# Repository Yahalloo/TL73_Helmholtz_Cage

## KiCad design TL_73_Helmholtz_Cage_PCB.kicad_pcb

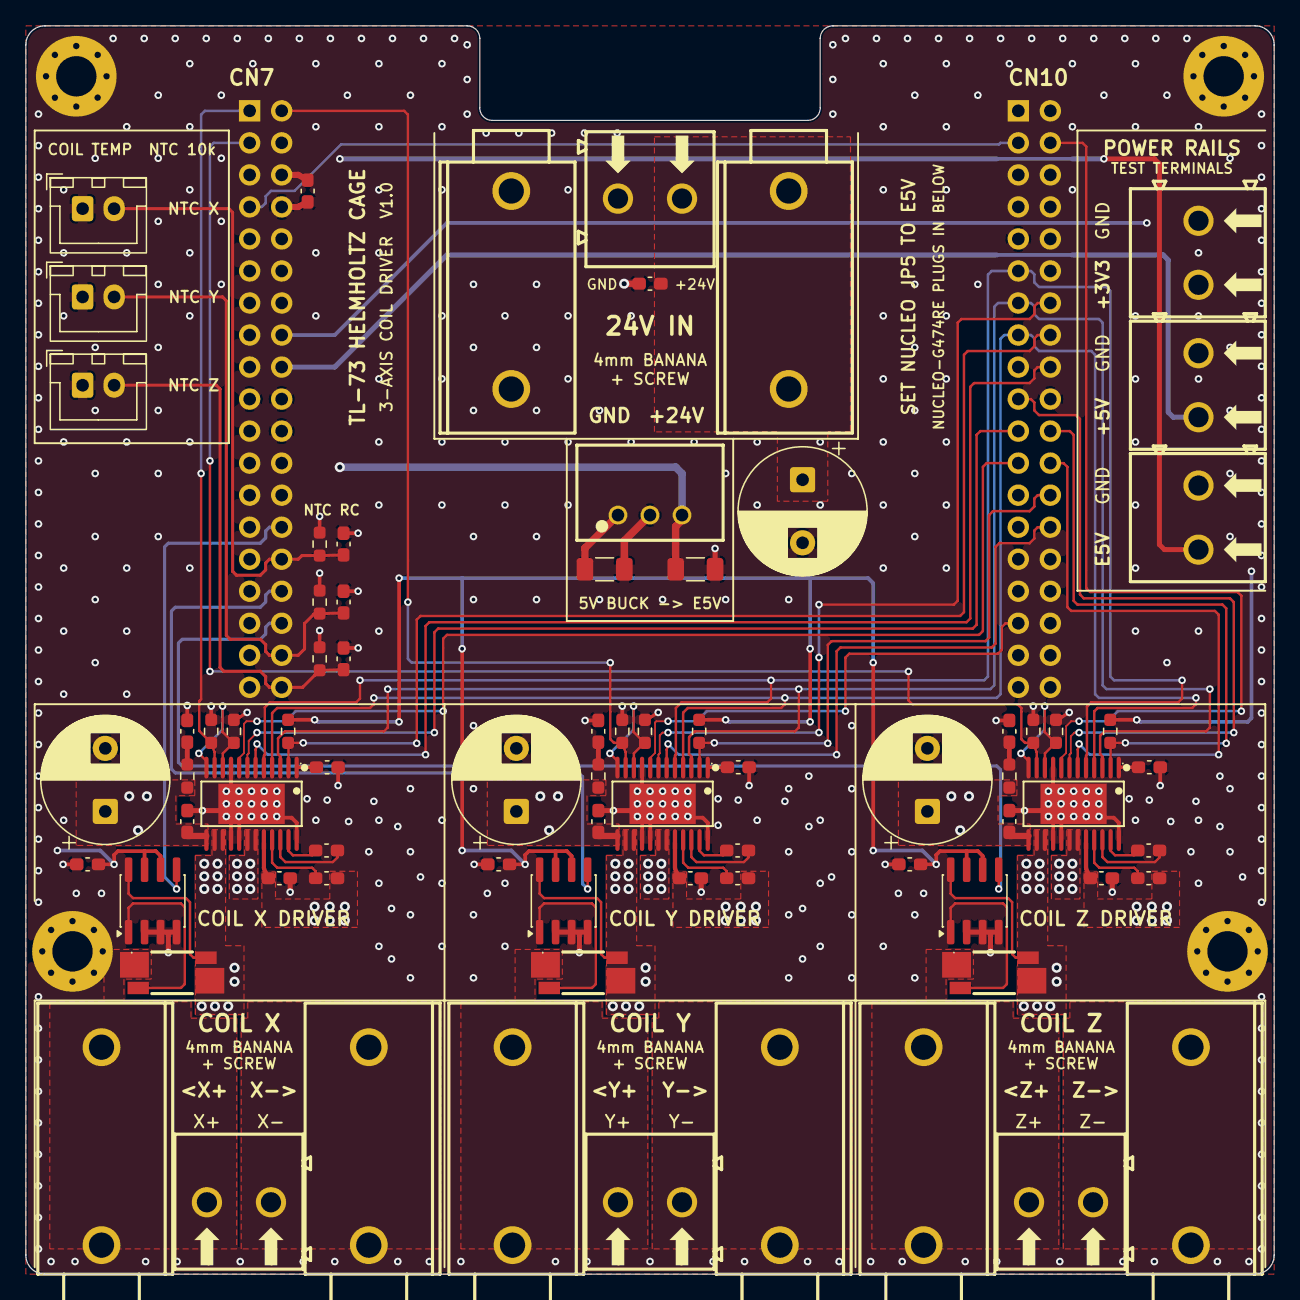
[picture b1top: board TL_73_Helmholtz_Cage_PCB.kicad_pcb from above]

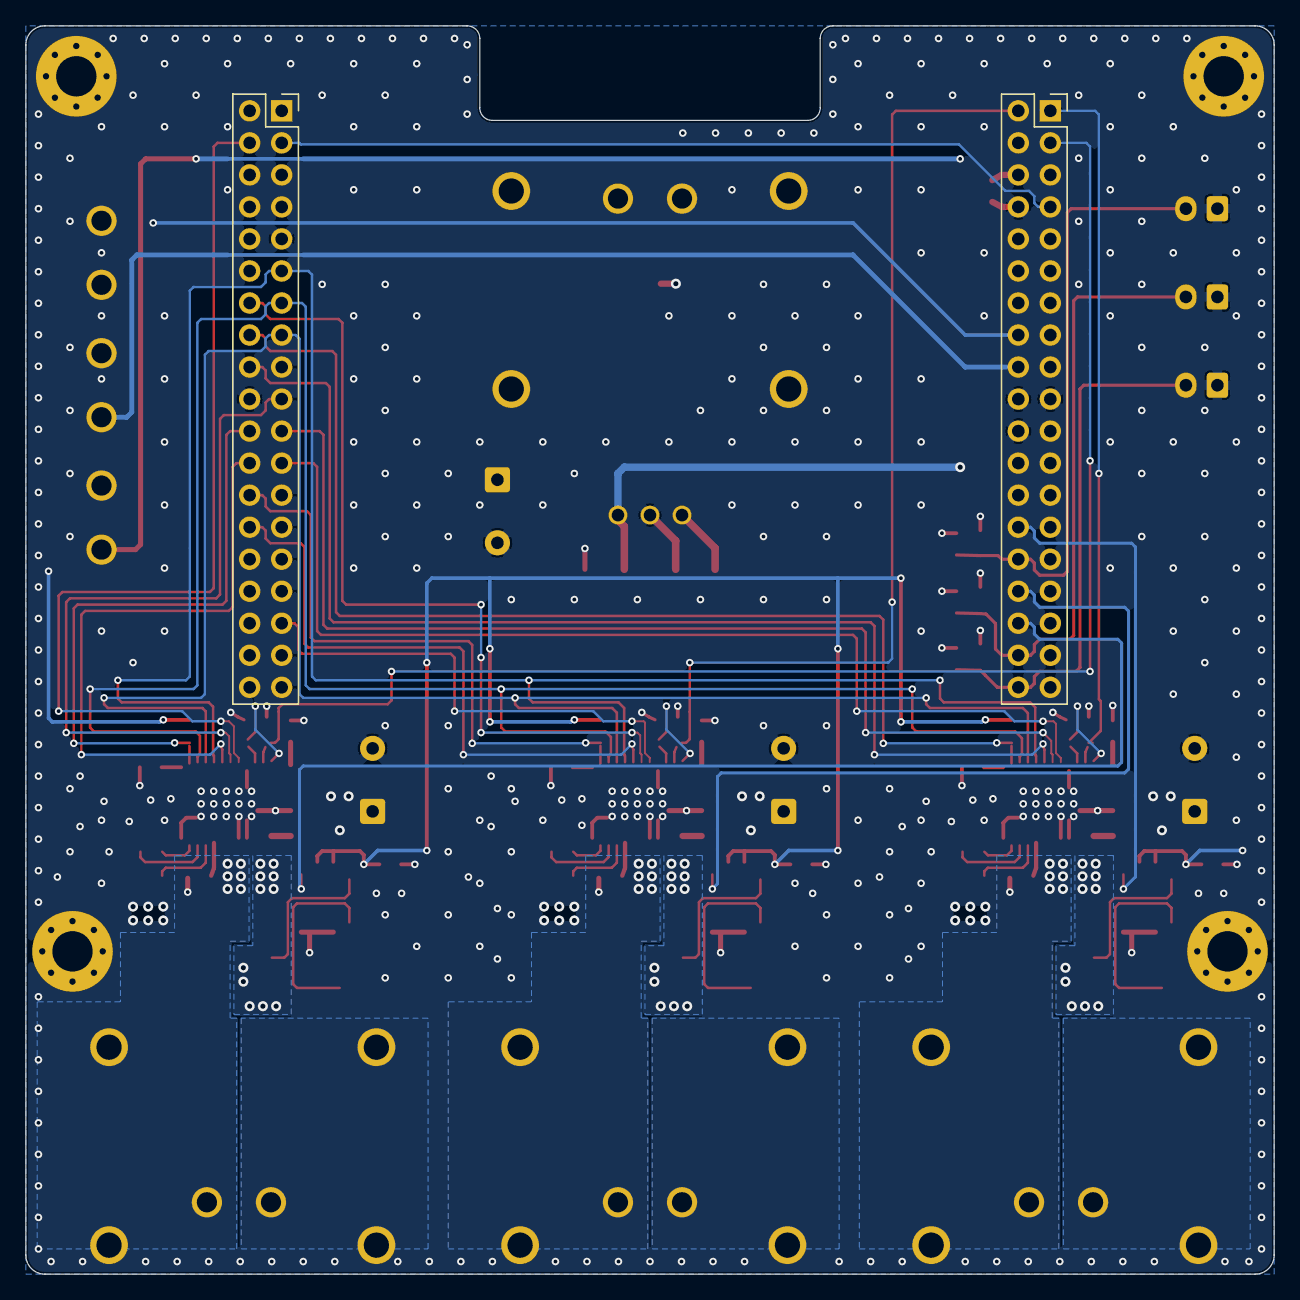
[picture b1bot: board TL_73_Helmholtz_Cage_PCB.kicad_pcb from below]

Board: 4 copper layers, 99.0 x 99.0 mm, 81 parts (2 on the bottom side), 63 nets.

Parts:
C101: 10uF; C_1206_3216Metric_Pad1.33x1.80mm_HandSolder
C102: 22uF; C_1206_3216Metric_Pad1.33x1.80mm_HandSolder
C201, C302, C305, C402, C405, C502, C505, C601, C701, C801, C901, C1001, C1101, C1202: 100nF; C_0603_1608Metric_Pad1.08x0.95mm_HandSolder
C301, C304, C401, C404, C501, C504: 1uF; C_0603_1608Metric_Pad1.08x0.95mm_HandSolder
C303, C403, C503: 47nF; C_0603_1608Metric_Pad1.08x0.95mm_HandSolder
C306, C406, C506: 10nF; C_0603_1608Metric_Pad1.08x0.95mm_HandSolder
C307, C407, C507, C1201: 1000uF; CP_Radial_D10.0mm_P5.00mm
CN1201: 24.243.1; CONN-TH_24.243.1_RED
CN1202: 24.243.2; CONN-TH_24.243.2
CN1203, CN1205, CN1207: 24.243.3; CONN-TH_24.243.3
CN1204, CN1206, CN1208: 24.243.5; CONN-TH_24.243.2
H101, H102, H103, H104: MountingHole; MountingHole_3.2mm_M3_Pad_Via
J201: CN7; PinSocket_2x19_P2.54mm_Vertical
J202: CN10; PinSocket_2x19_P2.54mm_Vertical
J901, J1001, J1101: NTC_JST_XH; JST_XH_B2B-XH-A_1x02_P2.50mm_Vertical
R301, R302, R401, R402, R501, R502, R901, R1001, R1101: 10k; R_0603_1608Metric_Pad0.98x0.95mm_HandSolder
R303, R403, R503: 470Ω; R_0603_1608Metric_Pad0.98x0.95mm_HandSolder
R304, R404, R504: 3.3Ω; R_0603_1608Metric_Pad0.98x0.95mm_HandSolder
R601, R701, R801: 10mΩ; RES-SMD_L6.4-W3.2_WSK2512R0100FEA
U101: K7805-1000R3_C2992391; PWRM-TH_YLPTEC_K78XX-1000R3
U301, U401, U501: DRV8873SPWPR; HTSSOP-24_L7.8-W4.4-P0.65-LS6.4-TL-EP
U601, U701, U801: INA240A1D; SOIC-8_3.9x4.9mm_P1.27mm
U1201, U1202, U1203, U1204, U1205, U1206, U1207: KF128-5.08-2P; CONN-TH_P5.08_KF128-5.08-2P

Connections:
+3V3: C601.1, C701.1, C801.1, J201.16, R301.1, R401.1, R501.1, R901.2, R1001.2, R1101.2, U601.6 (V+), U601.7 (REF1), U701.6 (V+), U701.7 (REF1), U801.6 (V+), U801.7 (REF1), U1207.1
+5V: J201.18, U1205.1
+24V: C101.1, C302.1, C304.1, C305.1, C307.1, C402.1, C404.1, C405.1, C407.1, C502.1, C504.1, C505.1, C507.1, C1201.1, C1202.1, CN1201.1, CN1201.2, R304.1, R404.1, R504.1, U101.1 (VIN), U301.13 (13VM), U301.20 (20VM), U401.13 (13VM), U401.20 (20VM), U501.13 (13VM), U501.20 (20VM), U1202.1
/CurrentSense_CoilX/Icoil1: R601.4 (I1), U301.14 (14OUT2), U301.15 (15OUT2)
/CurrentSense_CoilX/Icoil2: CN1203.1, CN1203.2, R601.1 (I2), U1201.1
/CurrentSense_CoilX/SENSE_N: R601.2 (E2), U601.1 (-)
/CurrentSense_CoilX/SENSE_P: R601.3 (E1), U601.8 (+)
/CurrentSense_CoilY/Icoil1: R701.4 (I1), U401.14 (14OUT2), U401.15 (15OUT2)
/CurrentSense_CoilY/Icoil2: CN1205.1, CN1205.2, R701.1 (I2), U1203.1
/CurrentSense_CoilY/SENSE_N: R701.2 (E2), U701.1 (-)
/CurrentSense_CoilY/SENSE_P: R701.3 (E1), U701.8 (+)
/CurrentSense_CoilZ/Icoil1: R801.4 (I1), U501.14 (14OUT2), U501.15 (15OUT2)
/CurrentSense_CoilZ/Icoil2: CN1207.1, CN1207.2, R801.1 (I2), U1206.1
/CurrentSense_CoilZ/SENSE_N: R801.2 (E2), U801.1 (-)
/CurrentSense_CoilZ/SENSE_P: R801.3 (E1), U801.8 (+)
/External_Connectors/CoilX-: CN1204.1, CN1204.2, U301.18 (18OUT1), U301.19 (19OUT1), U1201.2
/External_Connectors/CoilY-: CN1206.1, CN1206.2, U401.18 (18OUT1), U401.19 (19OUT1), U1203.2
/External_Connectors/CoilZ-: CN1208.1, CN1208.2, U501.18 (18OUT1), U501.19 (19OUT1), U1206.2
/ISENSE_CoilX: J201.28, U601.5
/ISENSE_CoilY: J201.32, U701.5
/ISENSE_CoilZ: J201.34, U801.5
/Nucleo_G474RE/PB8-BOOT0: J201.7, J202.3
/PWM_A_CoilX: J202.23, U301.8 (8PH/IN2)
/PWM_A_CoilY: J202.33, U401.8 (8PH/IN2)
/PWM_A_CoilZ: J202.4, U501.8 (8PH/IN2)
/PWM_B_CoilX: J202.21, U301.7 (7EN/IN1)
/PWM_B_CoilY: J202.14, U401.7 (7EN/IN1)
/PWM_B_CoilZ: J202.19, U501.7 (7EN/IN1)
/SPI_SCLK: J202.11, U301.5 (5SCLK), U401.5 (5SCLK), U501.5 (5SCLK)
/SPI_SDI: J202.15, U301.4 (4SDI), U401.4 (4SDI), U501.4 (4SDI)
/SPI_SDO: J202.13, U301.3 (3SDO), U401.3 (3SDO), U501.3 (3SDO)
/Temp_SenseX: C901.1, J201.30, J901.2, R901.1
/Temp_SenseY: C1001.1, J201.36, J1001.2, R1001.1
/Temp_SenseZ: C1101.1, J201.38, J1101.2, R1101.1
/~FAULT_CoilX: J202.16, R301.2, U301.2 (2nFAULT)
/~FAULT_CoilY: J202.26, R401.2, U401.2 (2nFAULT)
/~FAULT_CoilZ: J202.22, R501.2, U501.2 (2nFAULT)
/~SCS_CoilX: J202.18, U301.6 (6nSCS)
/~SCS_CoilY: J202.28, U401.6 (6nSCS)
/~SCS_CoilZ: J202.24, U501.6 (6nSCS)
/~SLEEP_CoilX: J201.1, R302.1, U301.11 (11NSLEEP)
/~SLEEP_CoilY: J201.2, R402.1, U401.11 (11NSLEEP)
/~SLEEP_CoilZ: J201.3, R502.1, U501.11 (11NSLEEP)
E5V: C102.1, C201.1, J201.6, U101.3 (+VO), U1204.1
GND: C101.2, C102.2, C201.2, C301.2, C302.2, C305.2, C306.2, C307.2, C401.2, C402.2, C405.2, C406.2, C407.2, C501.2, C502.2, C505.2, C506.2, C507.2, C601.2, C701.2, C801.2, C901.2, C1001.2, C1101.2, C1201.2, C1202.2, CN1202.1, CN1202.2, J201.8, J201.19, J201.20, J201.22, J202.9, J202.20, J901.1, J1001.1, J1101.1, R302.2, R303.2, R402.2, R403.2, R502.2, R503.2, U101.2 (GND), U301.9 (9DISABLE), U301.16 (16SRC), U301.17 (17SRC), U301.24 (24GND), U301.25 (EP), U401.9 (9DISABLE), U401.16 (16SRC), U401.17 (17SRC), U401.24 (24GND), U401.25 (EP), U501.9 (9DISABLE), U501.16 (16SRC), U501.17 (17SRC), U501.24 (24GND), U501.25 (EP), U601.2 (GND), U601.3 (REF2), U601.4 (GND), U701.2 (GND), U701.3 (REF2), U701.4 (GND), U801.2 (GND), U801.3 (REF2), U801.4 (GND), U1202.2, U1204.2, U1205.2, U1207.2
unnamed: C306.1, R304.2
unnamed: C406.1, R404.2
unnamed: C506.1, R504.2
unnamed: C301.1, U301.1 (1DVDD)
unnamed: R303.1, U301.10 (10IPROPL), U301.12 (12IPROPI2)
unnamed: C304.2, U301.21 (21VCP)
unnamed: C303.2, U301.22 (22CPH)
unnamed: C303.1, U301.23 (23CPL)
unnamed: C401.1, U401.1 (1DVDD)
unnamed: R403.1, U401.10 (10IPROPL), U401.12 (12IPROPI2)
unnamed: C404.2, U401.21 (21VCP)
unnamed: C403.2, U401.22 (22CPH)
unnamed: C403.1, U401.23 (23CPL)
unnamed: C501.1, U501.1 (1DVDD)
unnamed: R503.1, U501.10 (10IPROPL), U501.12 (12IPROPI2)
unnamed: C504.2, U501.21 (21VCP)
unnamed: C503.2, U501.22 (22CPH)
unnamed: C503.1, U501.23 (23CPL)

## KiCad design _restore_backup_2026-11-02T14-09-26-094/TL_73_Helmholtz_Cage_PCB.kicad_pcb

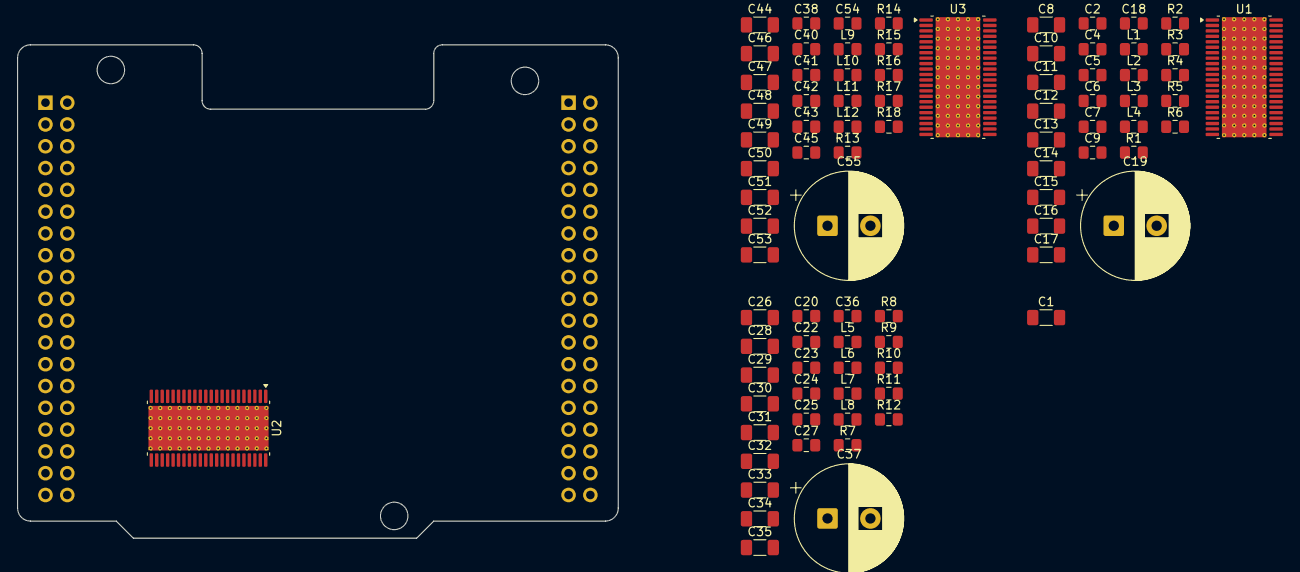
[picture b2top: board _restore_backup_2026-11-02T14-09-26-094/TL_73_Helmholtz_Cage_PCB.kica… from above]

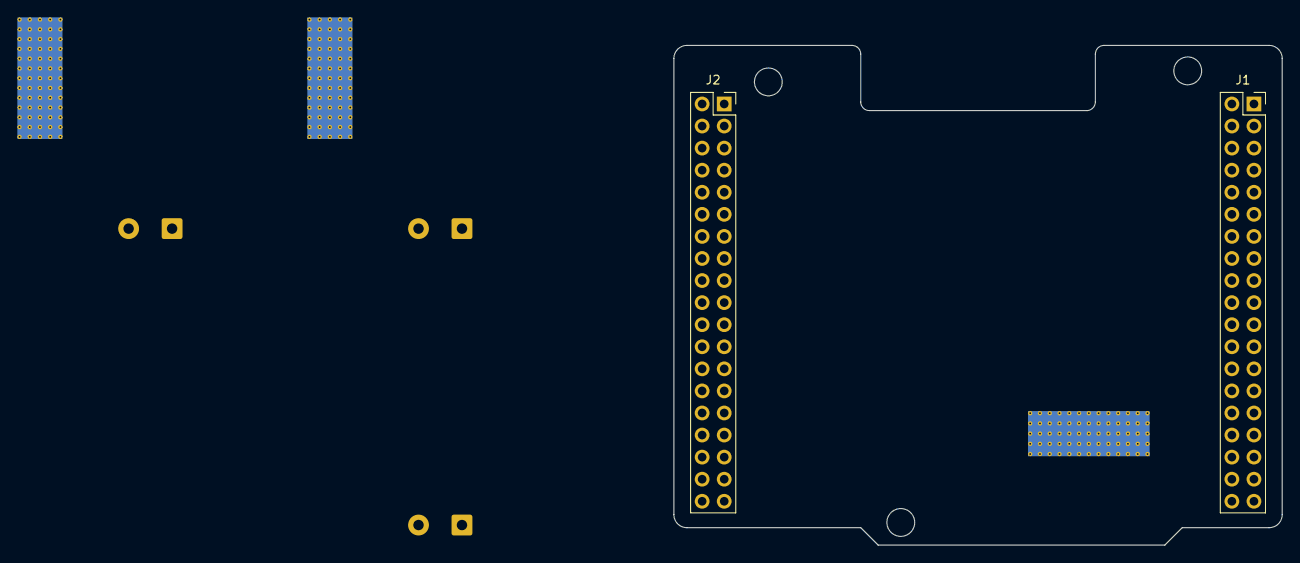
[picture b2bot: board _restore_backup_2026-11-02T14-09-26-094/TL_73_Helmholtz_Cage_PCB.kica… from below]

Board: 2 copper layers, 70.0 x 57.5 mm, 90 parts (2 on the bottom side), 64 nets, no tracks yet.

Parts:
C1, C8, C10, C11, C12, C13, C14, C15, C16, C17, C26, C28, C29, C30, C31, C32, C33, C34, C35, C44, C46, C47, C48, C49, C50, C51, C52, C53: 100nF; C_1206_3216Metric_Pad1.33x1.80mm_HandSolder
C2, C5, C6, C7, C9, C20, C23, C24, C25, C27, C38, C41, C42, C43, C45: 1uF; C_0805_2012Metric_Pad1.18x1.45mm_HandSolder
C4, C22, C40: 47uF; C_0805_2012Metric_Pad1.18x1.45mm_HandSolder
C18, C36, C54: 10 nF; C_0805_2012Metric_Pad1.18x1.45mm_HandSolder
C19, C37, C55: 1000uF; CP_Radial_D12.5mm_P5.00mm
H1, H2, H3: MountingHole; MountingHole_3.2mm_M3
J1: CN7; PinSocket_2x19_P2.54mm_Vertical
J2: CN10; PinSocket_2x19_P2.54mm_Vertical
L1, L2, L3, L4, L5, L6, L7, L8, L9, L10, L11, L12: 30Ω@100MHz; C_0805_2012Metric_Pad1.18x1.45mm_HandSolder
R1, R2, R3, R7, R8, R9, R13, R14, R15: 10k; C_0805_2012Metric_Pad1.18x1.45mm_HandSolder
R4, R10, R16: 1; C_0805_2012Metric_Pad1.18x1.45mm_HandSolder
R5, R11, R17: 36k; C_0805_2012Metric_Pad1.18x1.45mm_HandSolder
R6, R12, R18: 3.3; C_0805_2012Metric_Pad1.18x1.45mm_HandSolder
U1, U2, U3: DRV8412; HTSSOP-44-1EP_6.1x14mm_P0.635mm_EP5.2x14mm_Mask4.31x8.26mm_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

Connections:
+3V3: J1.16, R1.1, R3.1, R7.1, R9.1, R13.1, R15.1
+12V: C1.1, J1.24
+24V: C10.2, C11.2, C12.2, C17.2, C19.1, C28.2, C29.2, C30.2, C35.2, C37.1, C46.2, C47.2, C48.2, C53.2, C55.1, R6.1, R12.1, R18.1, U1.26 (PVDD_A), U1.27 (PVDD_A), U1.32 (PVDD_B), U1.35 (PVDD_C), U1.40 (PVDD_D), U1.41 (PVDD_D), U2.26 (PVDD_A), U2.27 (PVDD_A), U2.32 (PVDD_B), U2.35 (PVDD_C), U2.40 (PVDD_D), U2.41 (PVDD_D), U3.26 (PVDD_A), U3.27 (PVDD_A), U3.32 (PVDD_B), U3.35 (PVDD_C), U3.40 (PVDD_D), U3.41 (PVDD_D)
/Current_Driver_Distribution/VOUTA_CoilX: L1.2, L2.2
/Current_Driver_Distribution/VOUTA_CoilY: L5.2, L6.2
/Current_Driver_Distribution/VOUTA_CoilZ: L9.2, L10.2
/Current_Driver_Distribution/VOUTB_CoilX: L3.2, L4.2
/Current_Driver_Distribution/VOUTB_CoilY: L7.2, L8.2
/Current_Driver_Distribution/VOUTB_CoilZ: L11.2, L12.2
/PWM_A_CoilX: J2.23, U1.17 (PWM_A)
/PWM_A_CoilY: J2.33, U2.17 (PWM_A)
/PWM_A_CoilZ: J2.4, U3.17 (PWM_A)
/PWM_B_CoilX: J2.21, U1.15 (PWM_B)
/PWM_B_CoilY: J2.14, U2.15 (PWM_B)
/PWM_B_CoilZ: J2.19, U3.15 (PWM_B)
/~FAULT_CoilX: J2.16, R3.2, U1.18 (~FAULT)
/~FAULT_CoilY: J2.26, R9.2, U2.18 (~FAULT)
/~FAULT_CoilZ: J2.22, R15.2, U3.18 (~FAULT)
/~OTW_CoilX: J2.18, R1.2, U1.21 (~OTW)
/~OTW_CoilY: J2.28, R7.2, U2.21 (~OTW)
/~OTW_CoilZ: J2.24, R13.2, U3.21 (~OTW)
/~RESET_CoilX: J1.1, R2.1, U1.6 (~RESET_CD), U1.16 (~RESET_AB)
/~RESET_CoilY: J1.2, R8.1, U2.6 (~RESET_CD), U2.16 (~RESET_AB)
/~RESET_CoilZ: J1.3, R14.1, U3.6 (~RESET_CD), U3.16 (~RESET_AB)
GND: C1.2, C2.1, C4.2, C5.1, C6.1, C7.2, C9.1, C10.1, C11.1, C12.1, C17.1, C18.2, C19.2, C20.1, C22.2, C23.1, C24.1, C25.2, C27.1, C28.1, C29.1, C30.1, C35.1, C36.2, C37.2, C38.1, C40.2, C41.1, C42.1, C43.2, C45.1, C46.1, C47.1, C48.1, C53.1, C54.2, C55.2, J1.8, J1.19, J1.20, J1.22, J2.20, R2.2, R4.2, R8.2, R10.2, R14.2, R16.2, U1.3 (NC/GND), U1.4 (NC/GND), U1.5 (PWM_D), U1.7 (PWM_C), U1.13 (GND), U1.19 (NC/GND), U1.20 (NC/GND), U1.25 (NC/GND), U1.29 (GND_A), U1.30 (GND_B), U1.37 (GND_C), U1.38 (GND_D), U1.42 (NC/GND), U1.45 (EP), U2.3 (NC/GND), U2.4 (NC/GND), U2.5 (PWM_D), U2.7 (PWM_C), U2.13 (GND), U2.19 (NC/GND), U2.20 (NC/GND), U2.25 (NC/GND), U2.29 (GND_A), U2.30 (GND_B), U2.37 (GND_C), U2.38 (GND_D), U2.42 (NC/GND), U2.45 (EP), U3.3 (NC/GND), U3.4 (NC/GND), U3.5 (PWM_D), U3.7 (PWM_C), U3.13 (GND), U3.19 (NC/GND), U3.20 (NC/GND), U3.25 (NC/GND), U3.29 (GND_A), U3.30 (GND_B), U3.37 (GND_C), U3.38 (GND_D), U3.42 (NC/GND), U3.45 (EP)
unnamed: C18.1, R6.2
unnamed: C36.1, R12.2
unnamed: C54.1, R18.2
unnamed: C2.2, C4.1, C5.2, C6.2, C7.1, C9.2, U1.1 (GVDD_C), U1.2 (VDD), U1.22 (GVDD_B), U1.23 (GVDD_A), U1.44 (GVDD_D)
unnamed: C20.2, C22.1, C23.2, C24.2, C25.1, C27.2, U2.1 (GVDD_C), U2.2 (VDD), U2.22 (GVDD_B), U2.23 (GVDD_A), U2.44 (GVDD_D)
unnamed: C38.2, C40.1, C41.2, C42.2, C43.1, C45.2, U3.1 (GVDD_C), U3.2 (VDD), U3.22 (GVDD_B), U3.23 (GVDD_A), U3.44 (GVDD_D)
unnamed: C8.1, R4.1, R5.1, U1.8 (M1), U1.10 (M3), U1.12 (AGND)
unnamed: C13.1, U1.24 (BST_A)
unnamed: C14.1, U1.33 (BST_B)
unnamed: C15.1, U1.34 (BST_C)
unnamed: C16.1, U1.43 (BST_D)
unnamed: C8.2, U1.9 (M2), U1.11 (VREG)
unnamed: R5.2, U1.14 (OC_ADJ)
unnamed: C13.2, L1.1, U1.28 (OUT_A)
unnamed: C14.2, L2.1, U1.31 (OUT_B)
unnamed: C15.2, L3.1, U1.36 (OUT_C)
unnamed: C16.2, L4.1, U1.39 (OUT_D)
unnamed: C26.1, R10.1, R11.1, U2.8 (M1), U2.10 (M3), U2.12 (AGND)
unnamed: C31.1, U2.24 (BST_A)
unnamed: C32.1, U2.33 (BST_B)
unnamed: C33.1, U2.34 (BST_C)
unnamed: C34.1, U2.43 (BST_D)
unnamed: C26.2, U2.9 (M2), U2.11 (VREG)
unnamed: R11.2, U2.14 (OC_ADJ)
unnamed: C31.2, L5.1, U2.28 (OUT_A)
unnamed: C32.2, L6.1, U2.31 (OUT_B)
unnamed: C33.2, L7.1, U2.36 (OUT_C)
unnamed: C34.2, L8.1, U2.39 (OUT_D)
unnamed: C44.1, R16.1, R17.1, U3.8 (M1), U3.10 (M3), U3.12 (AGND)
unnamed: C49.1, U3.24 (BST_A)
unnamed: C50.1, U3.33 (BST_B)
unnamed: C51.1, U3.34 (BST_C)
unnamed: C52.1, U3.43 (BST_D)
unnamed: C44.2, U3.9 (M2), U3.11 (VREG)
unnamed: R17.2, U3.14 (OC_ADJ)
unnamed: C49.2, L9.1, U3.28 (OUT_A)
unnamed: C50.2, L10.1, U3.31 (OUT_B)
unnamed: C51.2, L11.1, U3.36 (OUT_C)
unnamed: C52.2, L12.1, U3.39 (OUT_D)
